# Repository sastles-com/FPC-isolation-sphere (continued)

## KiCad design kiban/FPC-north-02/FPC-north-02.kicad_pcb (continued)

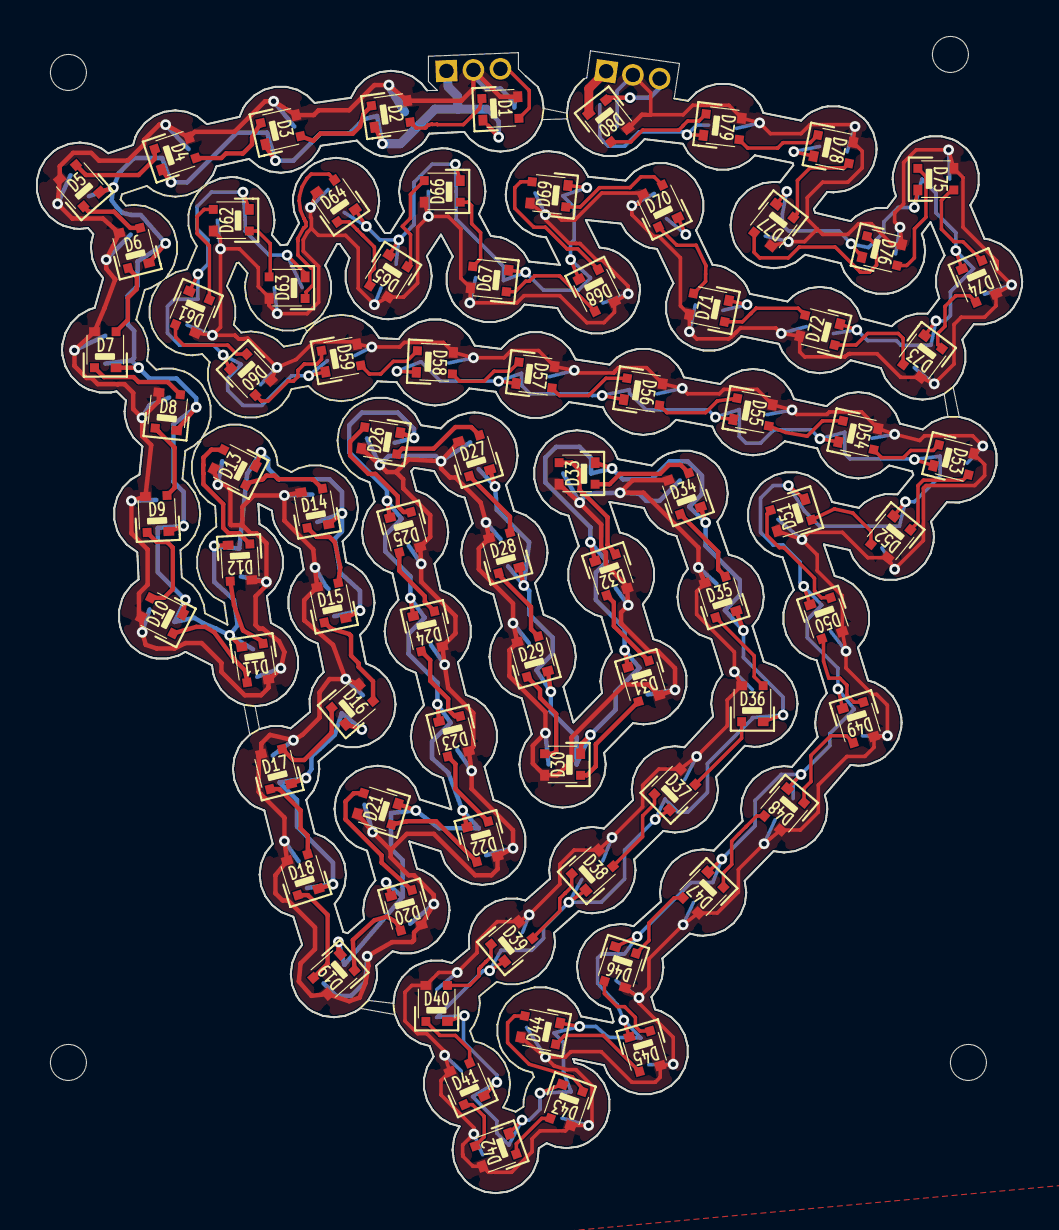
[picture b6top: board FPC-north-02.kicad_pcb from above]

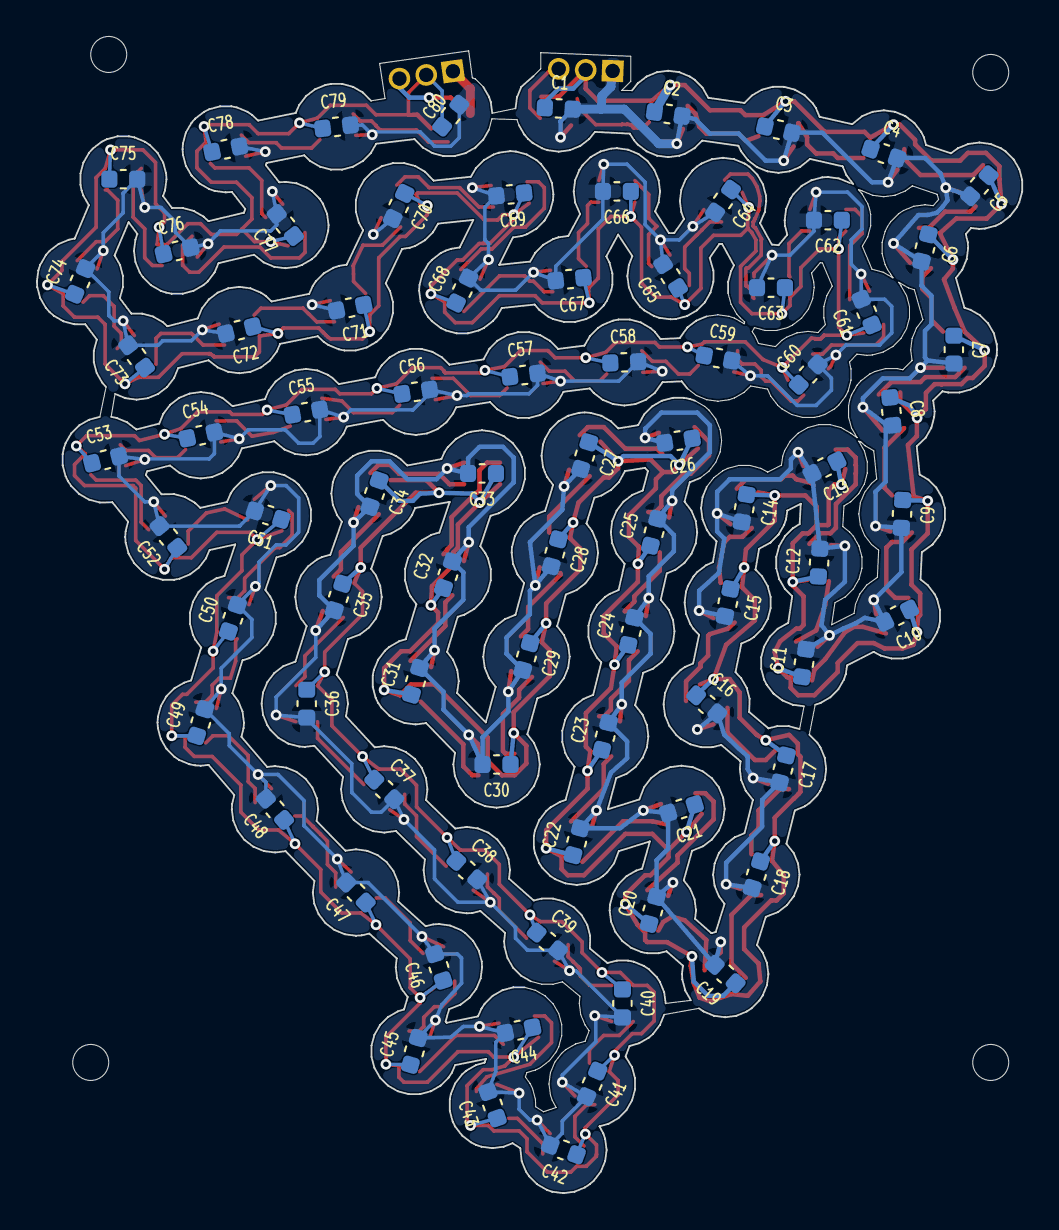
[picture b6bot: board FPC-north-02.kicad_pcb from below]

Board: 2 copper layers, 54.7 x 64.3 mm, 162 parts (80 on the bottom side), 83 nets.

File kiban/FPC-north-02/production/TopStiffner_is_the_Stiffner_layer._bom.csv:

Designator,Footprint,Quantity,Value,LCSC Part #
"C1, C10, C11, C12, C13, C14, C15, C16, C17, C18, C19, C2, C20, C21, C22, C23, C24, C25, C26, C27, C28, C29, C3, C30, C31, C32, C33, C34, C35, C36, C37, C38, C39, C4, C40, C41, C42, C43, C44, C45, C46, C47, C48, C49, C5, C50, C51, C52, C53, C54, C55, C56, C57, C58, C59, C6, C60, C61, C62, C63, C64, C65, C66, C67, C68, C69, C7, C70, C71, C72, C73, C74, C75, C76, C77, C78, C79, C8, C80, C9",0603,80,0.1uF,
"D1, D10, D11, D12, D13, D14, D15, D16, D17, D18, D19, D2, D20, D21, D22, D23, D24, D25, D26, D27, D28, D29, D3, D30, D31, D32, D33, D34, D35, D36, D37, D38, D39, D4, D40, D41, D42, D43, D44, D45, D46, D47, D48, D49, D5, D50, D51, D52, D53, D54, D55, D56, D57, D58, D59, D6, D60, D61, D62, D63, D64, D65, D66, D67, D68, D69, D7, D70, D71, D72, D73, D74, D75, D76, D77, D78, D79, D8, D80, D9",WS2812C-2020-nocut,80,WS2812B,
J1,PinHeader_1x03_P2.00mm_Vertical,1,IN,
J2,PinHeader_1x03_P2.00mm_Vertical,1,OUT,

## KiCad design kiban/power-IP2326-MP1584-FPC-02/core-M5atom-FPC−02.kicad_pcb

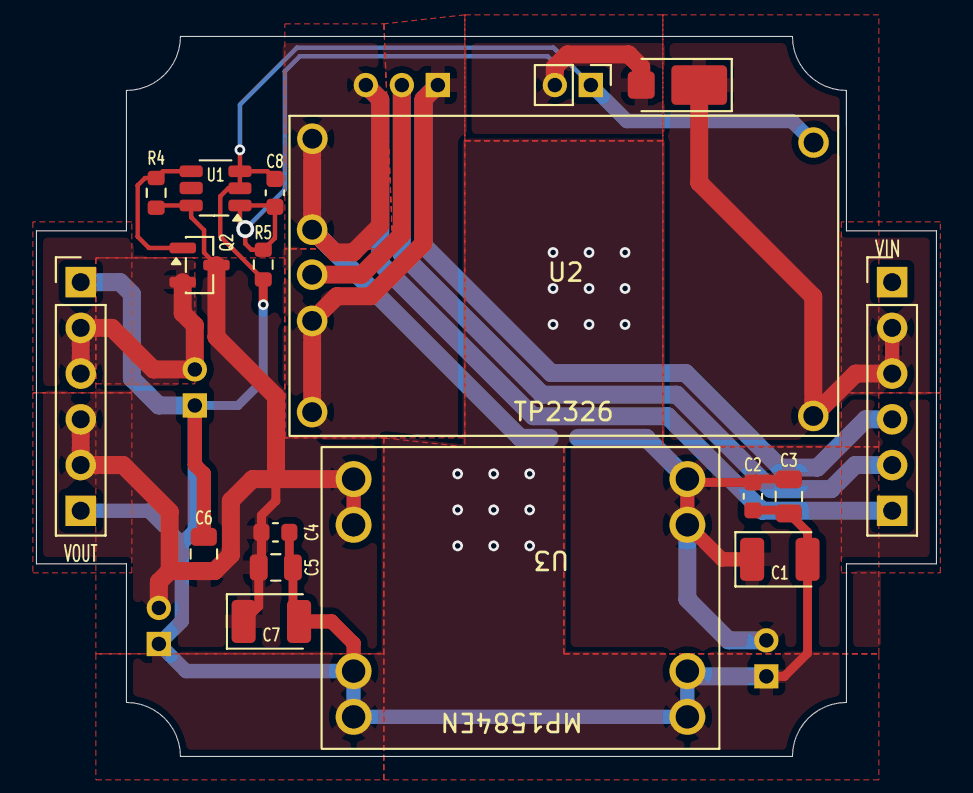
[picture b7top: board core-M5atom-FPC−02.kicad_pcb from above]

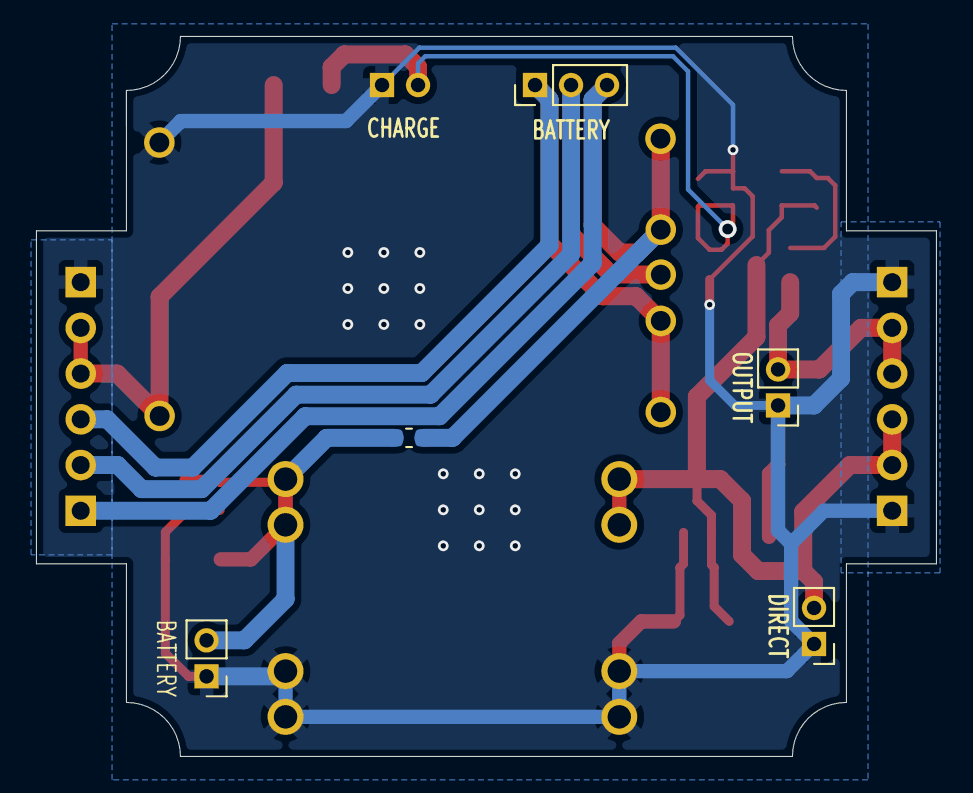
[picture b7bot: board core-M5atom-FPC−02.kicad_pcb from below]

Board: 2 copper layers, 50.0 x 40.0 mm, 23 parts (5 on the bottom side), 10 nets.

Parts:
C1, C7: 100uF; CP_EIA-3528-12_Kemet-T
C2, C4, C8: 0.1uF; C_0603_1608Metric
C3, C5, C6: 22uF; C_0805_2012Metric
D1: D_Schottky_Small; Vishay_SMPA
FB1: FerriteBead; L_0603_1608Metric
J1: BATTERY; PinHeader_1x03_P2.00mm_Vertical
J3: BATTERY; PinHeader_1x02_P2.00mm_Vertical
J4: DIRECT; PinHeader_1x02_P2.00mm_Vertical
J7: VOUT; PinHeader_1x06_P2.54mm_Vertical
J8: VIN; PinHeader_1x06_P2.54mm_Vertical
J9: OUTPUT; PinHeader_1x02_P2.00mm_Vertical
J14: CHARGE; PinHeader_1x02_P2.00mm_Vertical
Q2: AO3401A; SOT-23
R4: 10kΩ; R_0603_1608Metric
R5: 47kΩ; R_0603_1608Metric
U1: MAX16054; TSOT-23-6_HandSoldering
U2: TP2326; TS2326
U3: MP1584EN

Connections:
BM: J1.2, J8.5, U2.2 (BM)
CHARGE: D1.1 (K), J8.2, J8.3, U2.4 (VIN)
GATE: Q2.1 (G), R4.1, U1.4 (OUT_)
P+: FB1.1, J1.3, J8.6, U2.1 (B+)
P-: J1.1, J8.4, U2.3 (B-)
PGND: C1.2, C2.2, C3.2, C4.2, C5.2, C6.2, C7.2, C8.2, J3.1, J4.1, J7.1, J7.6, J8.1, J9.1, J14.1, R5.2, U1.2 (GND), U1.3 (CLR), U2.5 (GND), U3.1 (IN-), U3.4 (OUT-)
POWER: C8.1, D1.2 (A), J14.2, R5.1, U1.1 (IN)
VIN: C1.1, C2.1, C3.1, FB1.2, J3.2, U3.2 (IN+)
VOUT: C4.1, C5.1, C6.1, C7.1, J4.2, J7.4, J7.5, Q2.3 (D), R4.2, U1.6 (VCC), U3.3 (OUT+)
VOUT_SWITCHED: J7.2, J7.3, J9.2, Q2.2 (S)

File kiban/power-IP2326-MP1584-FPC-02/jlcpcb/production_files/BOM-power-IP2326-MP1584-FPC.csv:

Comment,Designator,Footprint,LCSC,Quantity
MAX16054,U1,TSOT-23-6_HandSoldering,,1
FerriteBead,FB1,L_0603_1608Metric,,1
D_Schottky_Small,D1,Vishay_SMPA,,1
100uF,C7,CP_EIA-3528-12_Kemet-T,,1
100uF,C1,CP_EIA-3528-12_Kemet-T,,1
47kΩ,R5,R_0603_1608Metric,,1
10kΩ,R4,R_0603_1608Metric,,1
AO3401A,Q2,SOT-23,,1
CHARGE,J14,PinHeader_1x02_P2.00mm_Vertical,,1
OUTPUT,J9,PinHeader_1x02_P2.00mm_Vertical,,1
DIRECT,J4,PinHeader_1x02_P2.00mm_Vertical,,1
BATTERY,J3,PinHeader_1x02_P2.00mm_Vertical,,1
BATTERY,J1,PinHeader_1x03_P2.00mm_Vertical,,1
0.1uF,C8,C_0603_1608Metric,,1
22uF,C6,C_0805_2012Metric,,1
22uF,C5,C_0805_2012Metric,,1
0.1uF,C4,C_0603_1608Metric,,1
22uF,C3,C_0805_2012Metric,,1
0.1uF,C2,C_0603_1608Metric,,1
MP1584EN,U3,MP1584EN,,1
TP2326,U2,TS2326,,1
VIN,J8,PinHeader_1x06_P2.54mm_Vertical,,1
VOUT,J7,PinHeader_1x06_P2.54mm_Vertical,,1
